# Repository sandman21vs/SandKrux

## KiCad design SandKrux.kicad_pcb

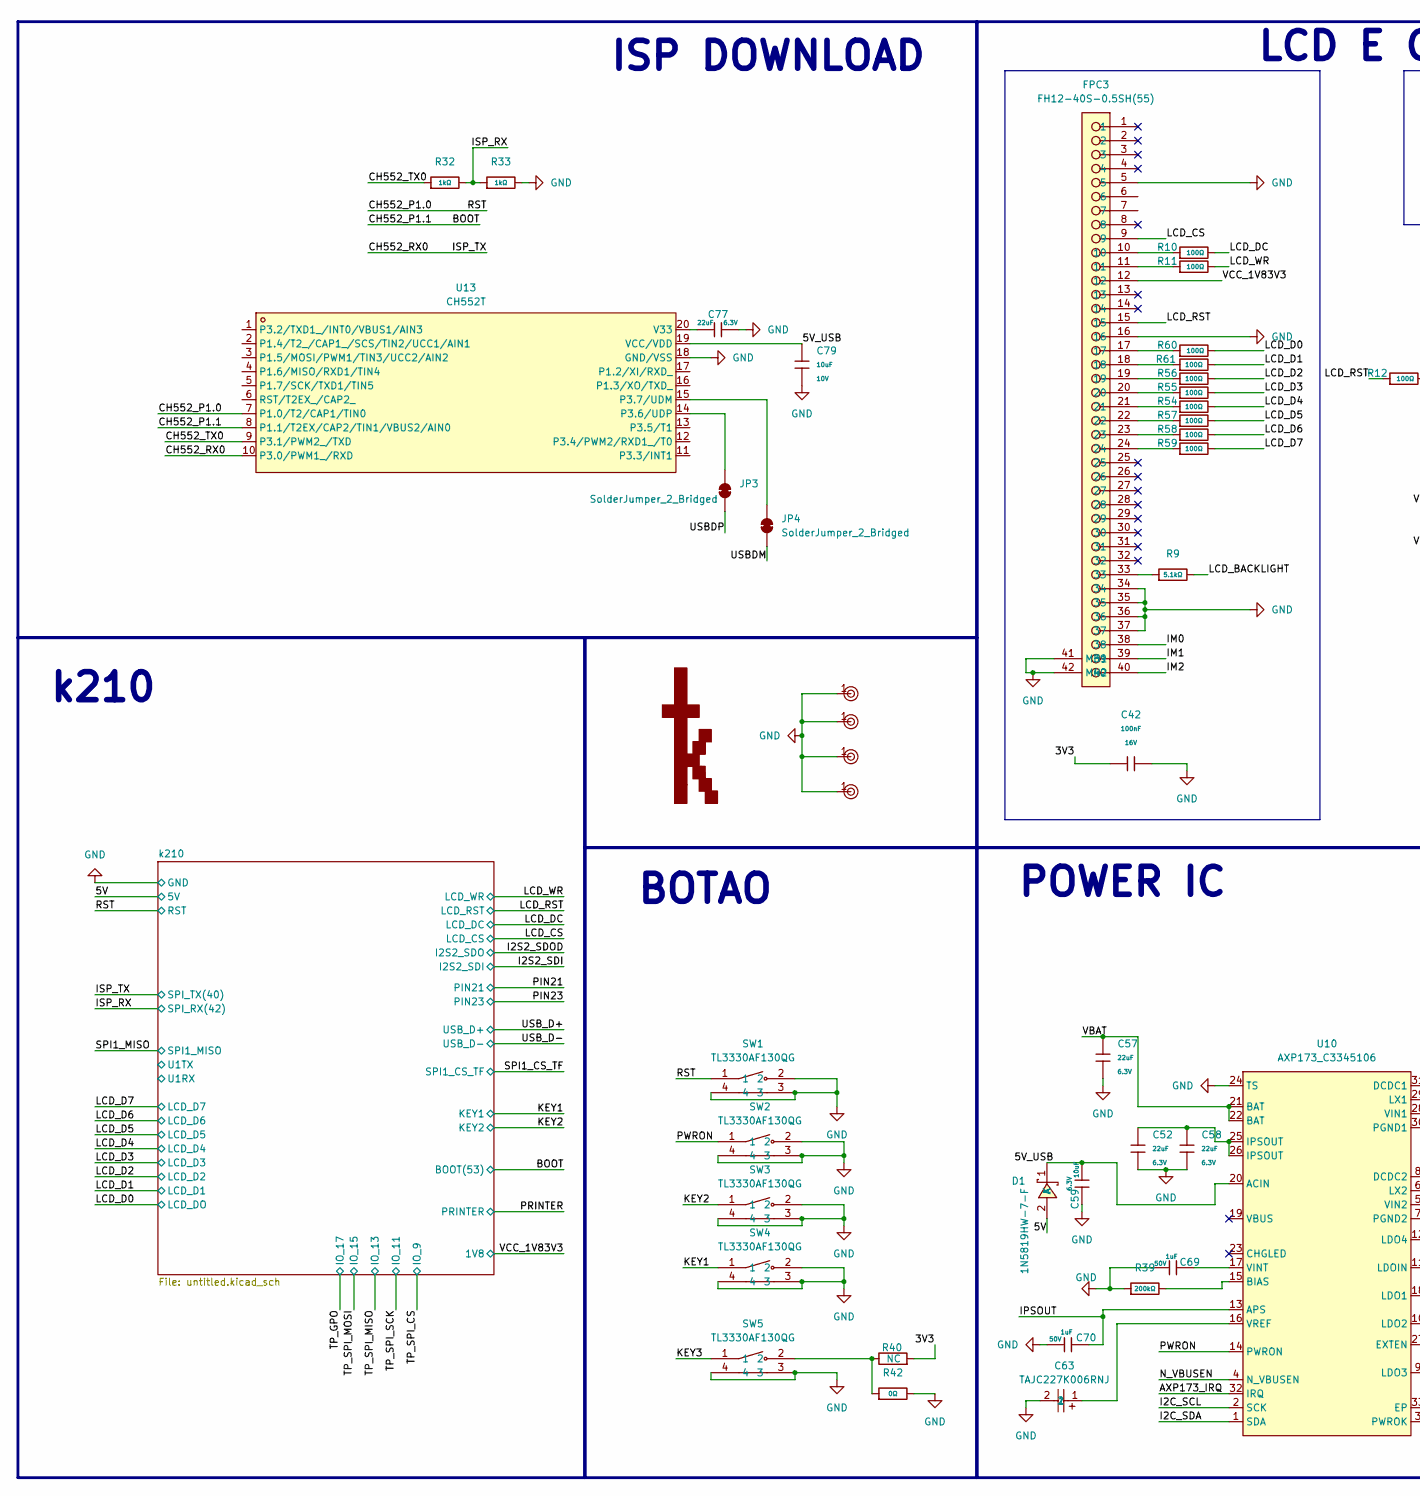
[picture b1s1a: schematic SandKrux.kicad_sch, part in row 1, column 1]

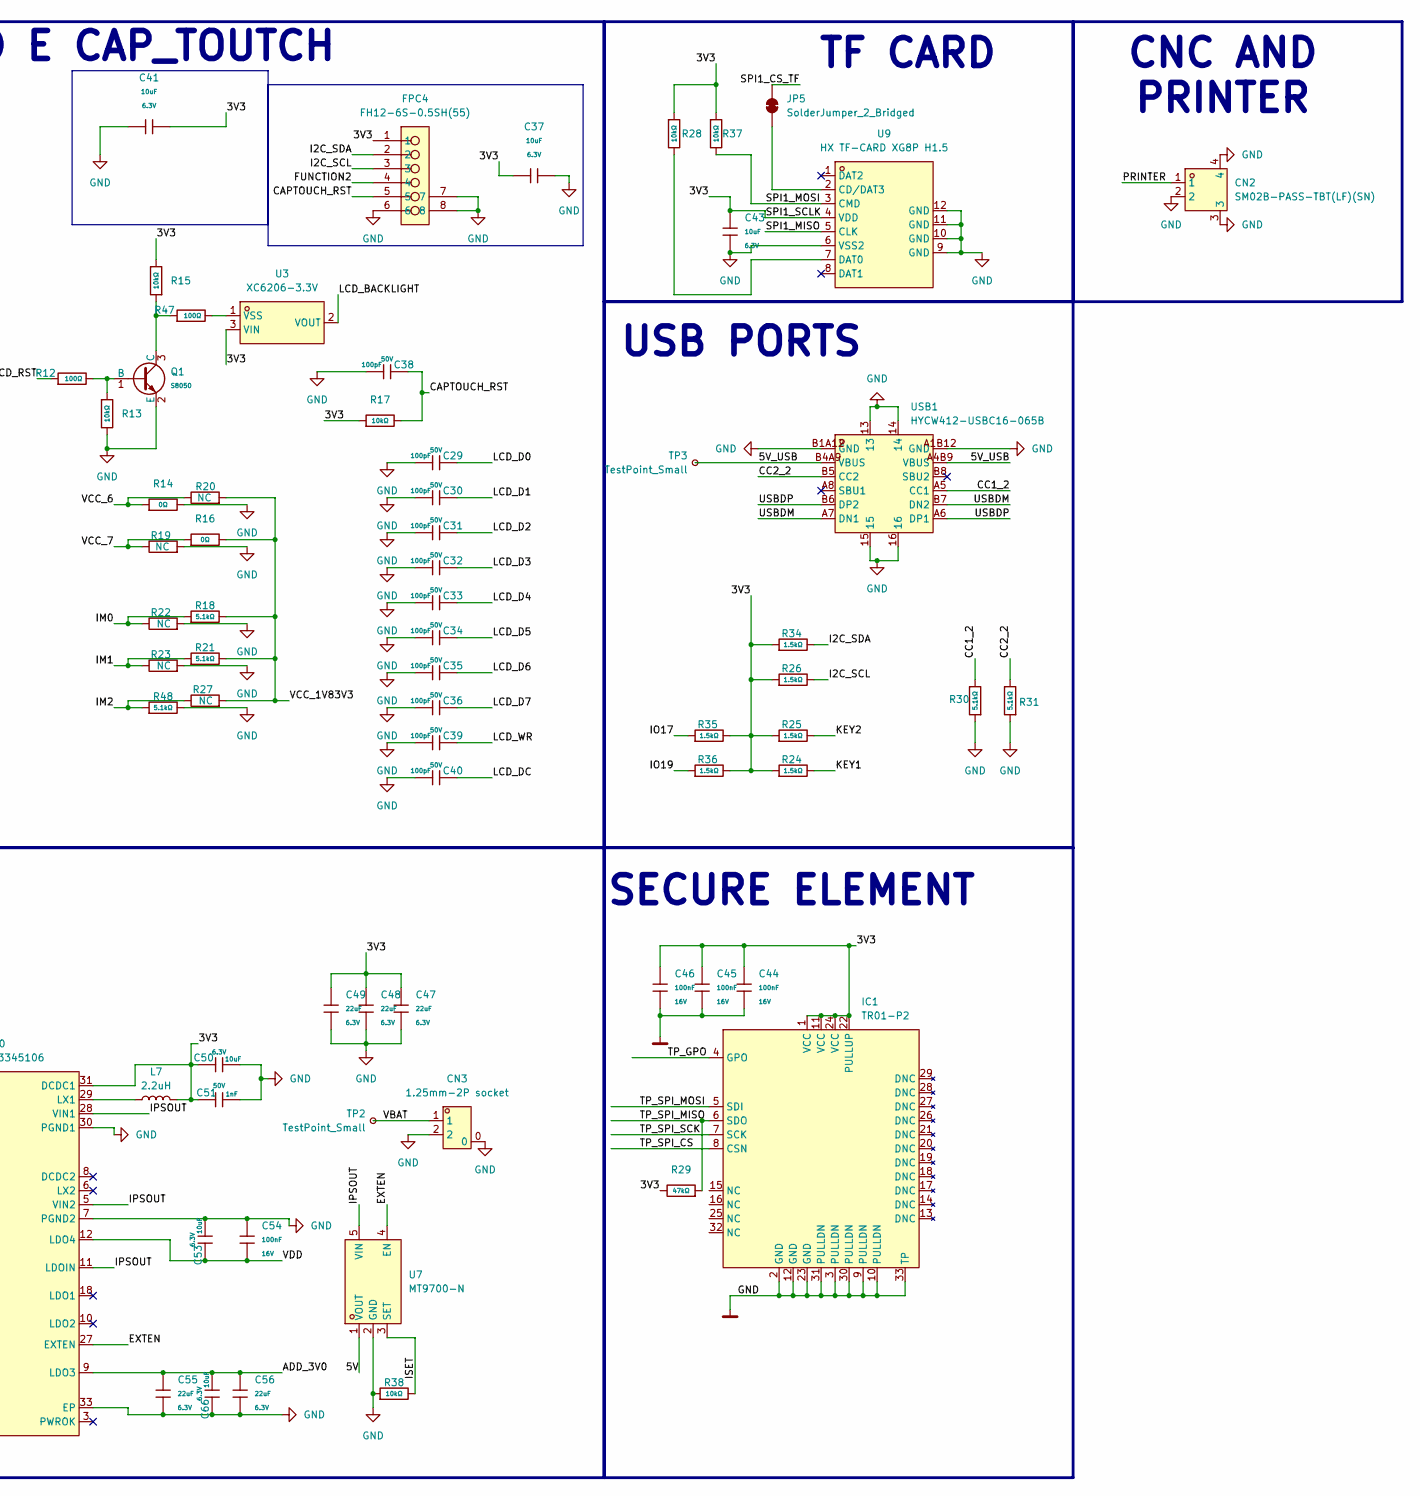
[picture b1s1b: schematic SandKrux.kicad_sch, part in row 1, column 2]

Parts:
C29, C30, C31, C32, C33, C34, C35, C36, C38, C39, C40: 100pF; C_0402; Voltage Rated 50V; Tolerance ±5%; Part 0402CG101J500NT; LCSC C1546
C37, C41, C43, C50, C53, C59, C66: 10uF; C_0402; Voltage Rated 6.3V; Tolerance ±20%; Part CL05A106MQ5NUNC; LCSC C15525
C42, C44, C45, C46, C54: 100nF; C_0402; Voltage Rated 16V; Tolerance ±10%; Part CL05B104KO5NNNC; LCSC C1525
C47, C48, C49, C52, C55, C56, C57, C58, C77: 22uF; C_0603; Voltage Rated 6.3V; Tolerance ±20%; Part CL10A226MQ8NRNC; LCSC C59461
C51: 1nF; C_0402; Voltage Rated 50V; Tolerance ±10%; Part 0402B102K500NT; LCSC C1523
C63: TAJC227K006RNJ; CAP-SMD_L6.0-W3.2-R-RD; LCSC Part C7216
C69, C70: 1uF; C_0603; Voltage Rated 50V; Tolerance ±10%; Part CL10A105KB8NNNC; LCSC C15849
C79: 10uF; C_0603; Voltage Rated 10V; Tolerance ±10%; Part CL10A106KP8NNNC; LCSC C19702
CN2: SM02B-PASS-TBT(LF)(SN); CONN-SMD_SM02B-PASS-TBT; LCSC Part C265417
CN3: 1.25mm-2P socket; CONN-SMD_1.25T-2P; LCSC Part C43462
D1: 1N5819HW-7-F; SOD-123_L2.7-W1.6-LS3.7-RD; LCSC Part C82544
FPC3: FH12-40S-0.5SH(55); FPC-SMD_FH12-40S-0.5SH-55; LCSC Part C202114
FPC4: FH12-6S-0.5SH(55); FPC-SMD_FH12-6S-0.5SH-55; LCSC Part C202118
H1, H2, H3, H4: Hole, 3mm
IC1: TR01-P2; QFN-32-1EP_4x4mm_P0.4mm_EP2.65x2.65mm
JP3, JP4, JP5: SolderJumper_2_Bridged; SolderJumper-2_P1.3mm_Bridged_RoundedPad1.0x1.5mm
L7: 2.2uH
Q1: S8050; Q_SOT-23; Part S8050; LCSC C364312
R9, R18, R21, R30, R31, R48: 5.1kΩ; R_0402; Overload Voltage (Max) 50V; Tolerance ±1%; Part 0402WGF5101TCE; LCSC C25905
R10, R11, R12, R47, R54, R55, R56, R57, R58, R59, R60, R61: 100Ω; R_0402; Overload Voltage (Max) 50V; Tolerance ±1%; Part 0402WGF1000TCE; LCSC C25076
R13, R15, R17, R28, R37, R38: 10kΩ; R_0402; Overload Voltage (Max) 50V; Tolerance ±1%; Part 0402WGF1002TCE; LCSC C25744
R14, R16, R42: 0Ω; R_0402; Overload Voltage (Max) 50V; Tolerance ±1%; Part 0402WGF0000TCE; LCSC C17168
R19, R20, R22, R23, R27, R40: NC; R_0201_0603Metric
R24, R25, R26, R34, R35, R36: 1.5kΩ; R_0402; Overload Voltage (Max) 50V; Tolerance ±1%; Part 0402WGF1501TCE; LCSC C25867
R29: 47kΩ; R_0402; Overload Voltage (Max) 50V; Tolerance ±1%; Part 0402WGF4702TCE; LCSC C25792
R32, R33: 1kΩ; R_0603; Overload Voltage (Max) 75V; Tolerance ±1%; Part 0603WAF1001T5E; LCSC C21190
R39: 200kΩ; R_0402; Overload Voltage (Max) 50V; Tolerance ±1%; Part 0402WGF2003TCE; LCSC C25764
SW1, SW2, SW3, SW4, SW5: TL3330AF130QG; SW-SMD_E-SWITCH_TL3330; LCSC Part C2886886
TP2, TP3: TestPoint_Small; TestPoint_Pad_D1.0mm
U3: XC6206-3.3V; SSOT-3_L2.9-W1.6-P0.95-LS2.8-BR; LCSC Part C2891841
U7: MT9700-N; SOT-23-5_L2.9-W1.6-P0.95-LS2.9-BL; LCSC Part C42441843
U9: HX TF-CARD XG8P H1.5; TF-SMD_HX-TF-CARD-XG8P-H1.5; LCSC Part C19189039
U10: AXP173_C3345106; QFN-32_L5.0-W5.0-P0.50-TL-EP3.5-1; LCSC Part C3345106
U13: CH552T; TSSOP-20_L6.5-W4.4-P0.65-LS6.4-BL; LCSC Part C111367
USB1: HYCW412-USBC16-065B; USB-C-SMD_HYCW412-USBC16-065B; LCSC Part C5342196

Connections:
/3V3: C37.1, C41.2, C42.1, C43.1, C44.1, C45.1, C46.1, C47.1, C48.1, C49.1, C50.1, C51.1, FPC4.1, IC1.1 (VCC), IC1.11 (VCC), IC1.22 (PULLUP), IC1.24 (VCC), L7.2, R15.2, R17.1, R24.1, R25.1, R26.1, R28.1, R29.2, R34.1, R35.2, R36.2, R37.1, R40.2, U3.3 (VIN), U9.4 (VDD), U10.31 (DCDC1)
/5V: D1.2 (A), U7.1 (VOUT); also elsewhere on the board
/5V_USB: C59.2, C79.1, D1.1 (K), TP3.1, U10.20 (ACIN), U13.19 (VCC/VDD), USB1.A4B9 (VBUS), USB1.B4A9 (VBUS)
/ADD_3V0: C55.1, C56.1, C66.2, U10.9 (LDO3)
/AXP173_IRQ: U10.32 (IRQ)
/BOOT: U13.8 (P1.1/T2EX/CAP2/TIN1/VBUS2/AIN0); also elsewhere on the board
/CAPTOUCH_RST: C38.2, FPC4.5, R17.2
/CC1_2: R30.2, USB1.A5 (CC1)
/CC2_2: R31.2, USB1.B5 (CC2)
/CH552_P1.0: SW1.1, U13.7 (P1.0/T2/CAP1/TIN0); also elsewhere on the board
/CH552_RX0: U13.10 (P3.0/PWM1_/RXD); also elsewhere on the board
/CH552_TX0: R32.1, U13.9 (P3.1/PWM2_/TXD)
/EXTEN: U7.4 (EN), U10.27 (EXTEN)
/FUNCTION2: FPC4.4
/I2C_SCL: FPC4.3, R26.2, U10.2 (SCK)
/I2C_SDA: FPC4.2, R34.2, U10.1 (SDA)
/IM0: FPC3.38, R18.1, R22.1
/IM1: FPC3.39, R21.1, R23.1
/IM2: FPC3.40, R27.1, R48.1
/IO17: R35.1
/IO19: R36.1
/IPSOUT: C70.2, U7.5 (VIN), U10.5 (VIN2), U10.11 (LDOIN), U10.13 (APS), U10.28 (VIN1)
/ISET: R38.2, U7.3 (SET)
/ISP_RX: R32.2, R33.1; also elsewhere on the board
/KEY1: R24.2, SW4.1; also elsewhere on the board
/KEY2: R25.2, SW3.1; also elsewhere on the board
/KEY3: SW5.1
/LCD_BACKLIGHT: R9.2, U3.2 (VOUT)
/LCD_CS: FPC3.9; also elsewhere on the board
/LCD_D0: C29.2, R60.2; also elsewhere on the board
/LCD_D1: C30.2, R61.2; also elsewhere on the board
/LCD_D2: C31.2, R56.2; also elsewhere on the board
/LCD_D3: C32.2, R55.2; also elsewhere on the board
/LCD_D4: C33.2, R54.2; also elsewhere on the board
/LCD_D5: C34.2, R57.2; also elsewhere on the board
/LCD_D6: C35.2, R58.2; also elsewhere on the board
/LCD_D7: C36.2, R59.2; also elsewhere on the board
/LCD_DC: C40.2, R10.2; also elsewhere on the board
/LCD_RST: FPC3.15, R12.1; also elsewhere on the board
/LCD_WR: C39.2, R11.2; also elsewhere on the board
/N_VBUSEN: U10.4 (N_VBUSEN)
/PRINTER: CN2.1; also elsewhere on the board
/PWRON: SW2.1, U10.14 (PWRON)
/SPI1_CS_TF: JP5.2 (B); also elsewhere on the board
/SPI1_MISO: U9.5 (CLK); also elsewhere on the board
/SPI1_MOSI: R37.2, U9.3 (CMD)
/TP_GPO: IC1.4 (GPO); also elsewhere on the board
/TP_SPI_CS: IC1.8 (CSN); also elsewhere on the board
/TP_SPI_MISO: IC1.6 (SDO), R29.1; also elsewhere on the board
/TP_SPI_MOSI: IC1.5 (SDI); also elsewhere on the board
/TP_SPI_SCK: IC1.7 (SCK); also elsewhere on the board
/USBDM: JP4.1 (A), USB1.A7 (DN1), USB1.B7 (DN2)
/USBDP: JP3.1 (A), USB1.A6 (DP1), USB1.B6 (DP2)
/VBAT: C57.1, CN3.1, TP2.1, U10.21 (BAT), U10.22 (BAT)
/VCC_1V83V3: FPC3.12, R16.2, R18.2, R20.2, R21.2, R27.2; also elsewhere on the board
/VCC_6: R14.1, R20.1
/VCC_7: R16.1, R19.1
/VDD: C53.1, C54.2, U10.12 (LDO4)
GND: C29.1, C30.1, C31.1, C32.1, C33.1, C34.1, C35.1, C36.1, C37.2, C38.1, C39.1, C40.1, C41.1, C42.2, C43.2, C44.2, C45.2, C46.2, C47.2, C48.2, C49.2, C50.2, C51.2, C52.2, C53.2, C54.1, C55.2, C56.2, C57.2, C58.2, C59.1, C63.2, C66.1, C69.1, C70.1, C77.2, C79.2, CN2.2, CN2.3, CN2.4, CN3.0, CN3.2, FPC3.5, FPC3.16, FPC3.34, FPC3.35, FPC3.36, FPC3.37, FPC3.41 (MH1), FPC3.42 (MH2), FPC4.6, FPC4.7, FPC4.8, H1.1, H2.1, H3.1, H4.1, IC1.2 (GND), IC1.3 (PULLDN), IC1.9 (PULLDN), IC1.10 (PULLDN), IC1.12 (GND), IC1.23 (GND), IC1.30 (PULLDN), IC1.31 (PULLDN), IC1.33 (TP), Q1.2 (E), R13.2, R14.2, R19.2, R22.2, R23.2, R30.1, R31.1, R33.2, R38.1, R39.1, R42.2, R48.2, SW1.2, SW1.3, SW1.4, SW2.2, SW2.3, SW2.4, SW3.2, SW3.3, SW3.4, SW4.2, SW4.3, SW4.4, SW5.3, SW5.4, U7.2 (GND), U9.6 (VSS2), U9.9 (GND), U9.10 (GND), U9.11 (GND), U9.12 (GND), U10.7 (PGND2), U10.24 (TS), U10.30 (PGND1), U10.33 (EP), U13.18 (GND/VSS), USB1.13, USB1.14, USB1.15, USB1.16, USB1.A1B12 (GND), USB1.B1A12 (GND); also elsewhere on the board
unnamed: C52.1, C58.1, U10.25 (IPSOUT), U10.26 (IPSOUT)
unnamed: FPC3.10, R10.1
unnamed: FPC3.11, R11.1
unnamed: FPC3.17, R60.1
unnamed: FPC3.18, R61.1
unnamed: FPC3.19, R56.1
unnamed: FPC3.20, R55.1
unnamed: FPC3.21, R54.1
unnamed: FPC3.22, R57.1
unnamed: FPC3.23, R58.1
unnamed: FPC3.24, R59.1
unnamed: FPC3.33, R9.1
unnamed: JP3.2 (B), U13.14 (P3.6/UDP)
unnamed: JP4.2 (B), U13.15 (P3.7/UDM)
unnamed: JP5.1 (A), U9.2 (CD/DAT3)
unnamed: Q1.1 (B), R12.2, R13.1
unnamed: Q1.3 (C), R15.1, R47.1
unnamed: R40.1, R42.1, SW5.2
unnamed: R47.2, U3.1 (VSS)
unnamed: R28.2, U9.7 (DAT0)
unnamed: R39.2, U10.15 (BIAS)
unnamed: L7.1, U10.29 (LX1)
unnamed: C69.2, U10.17 (VINT)
unnamed: C63.1, U10.16 (VREF)
unnamed: C77.1, U13.20 (V33)

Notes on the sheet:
TF CARD
LCD E CAP_TOUTCH
POWER IC
BOTAO
k210
ISP DOWNLOAD
USB PORTS
SECURE ELEMENT
CNC AND PRINTER

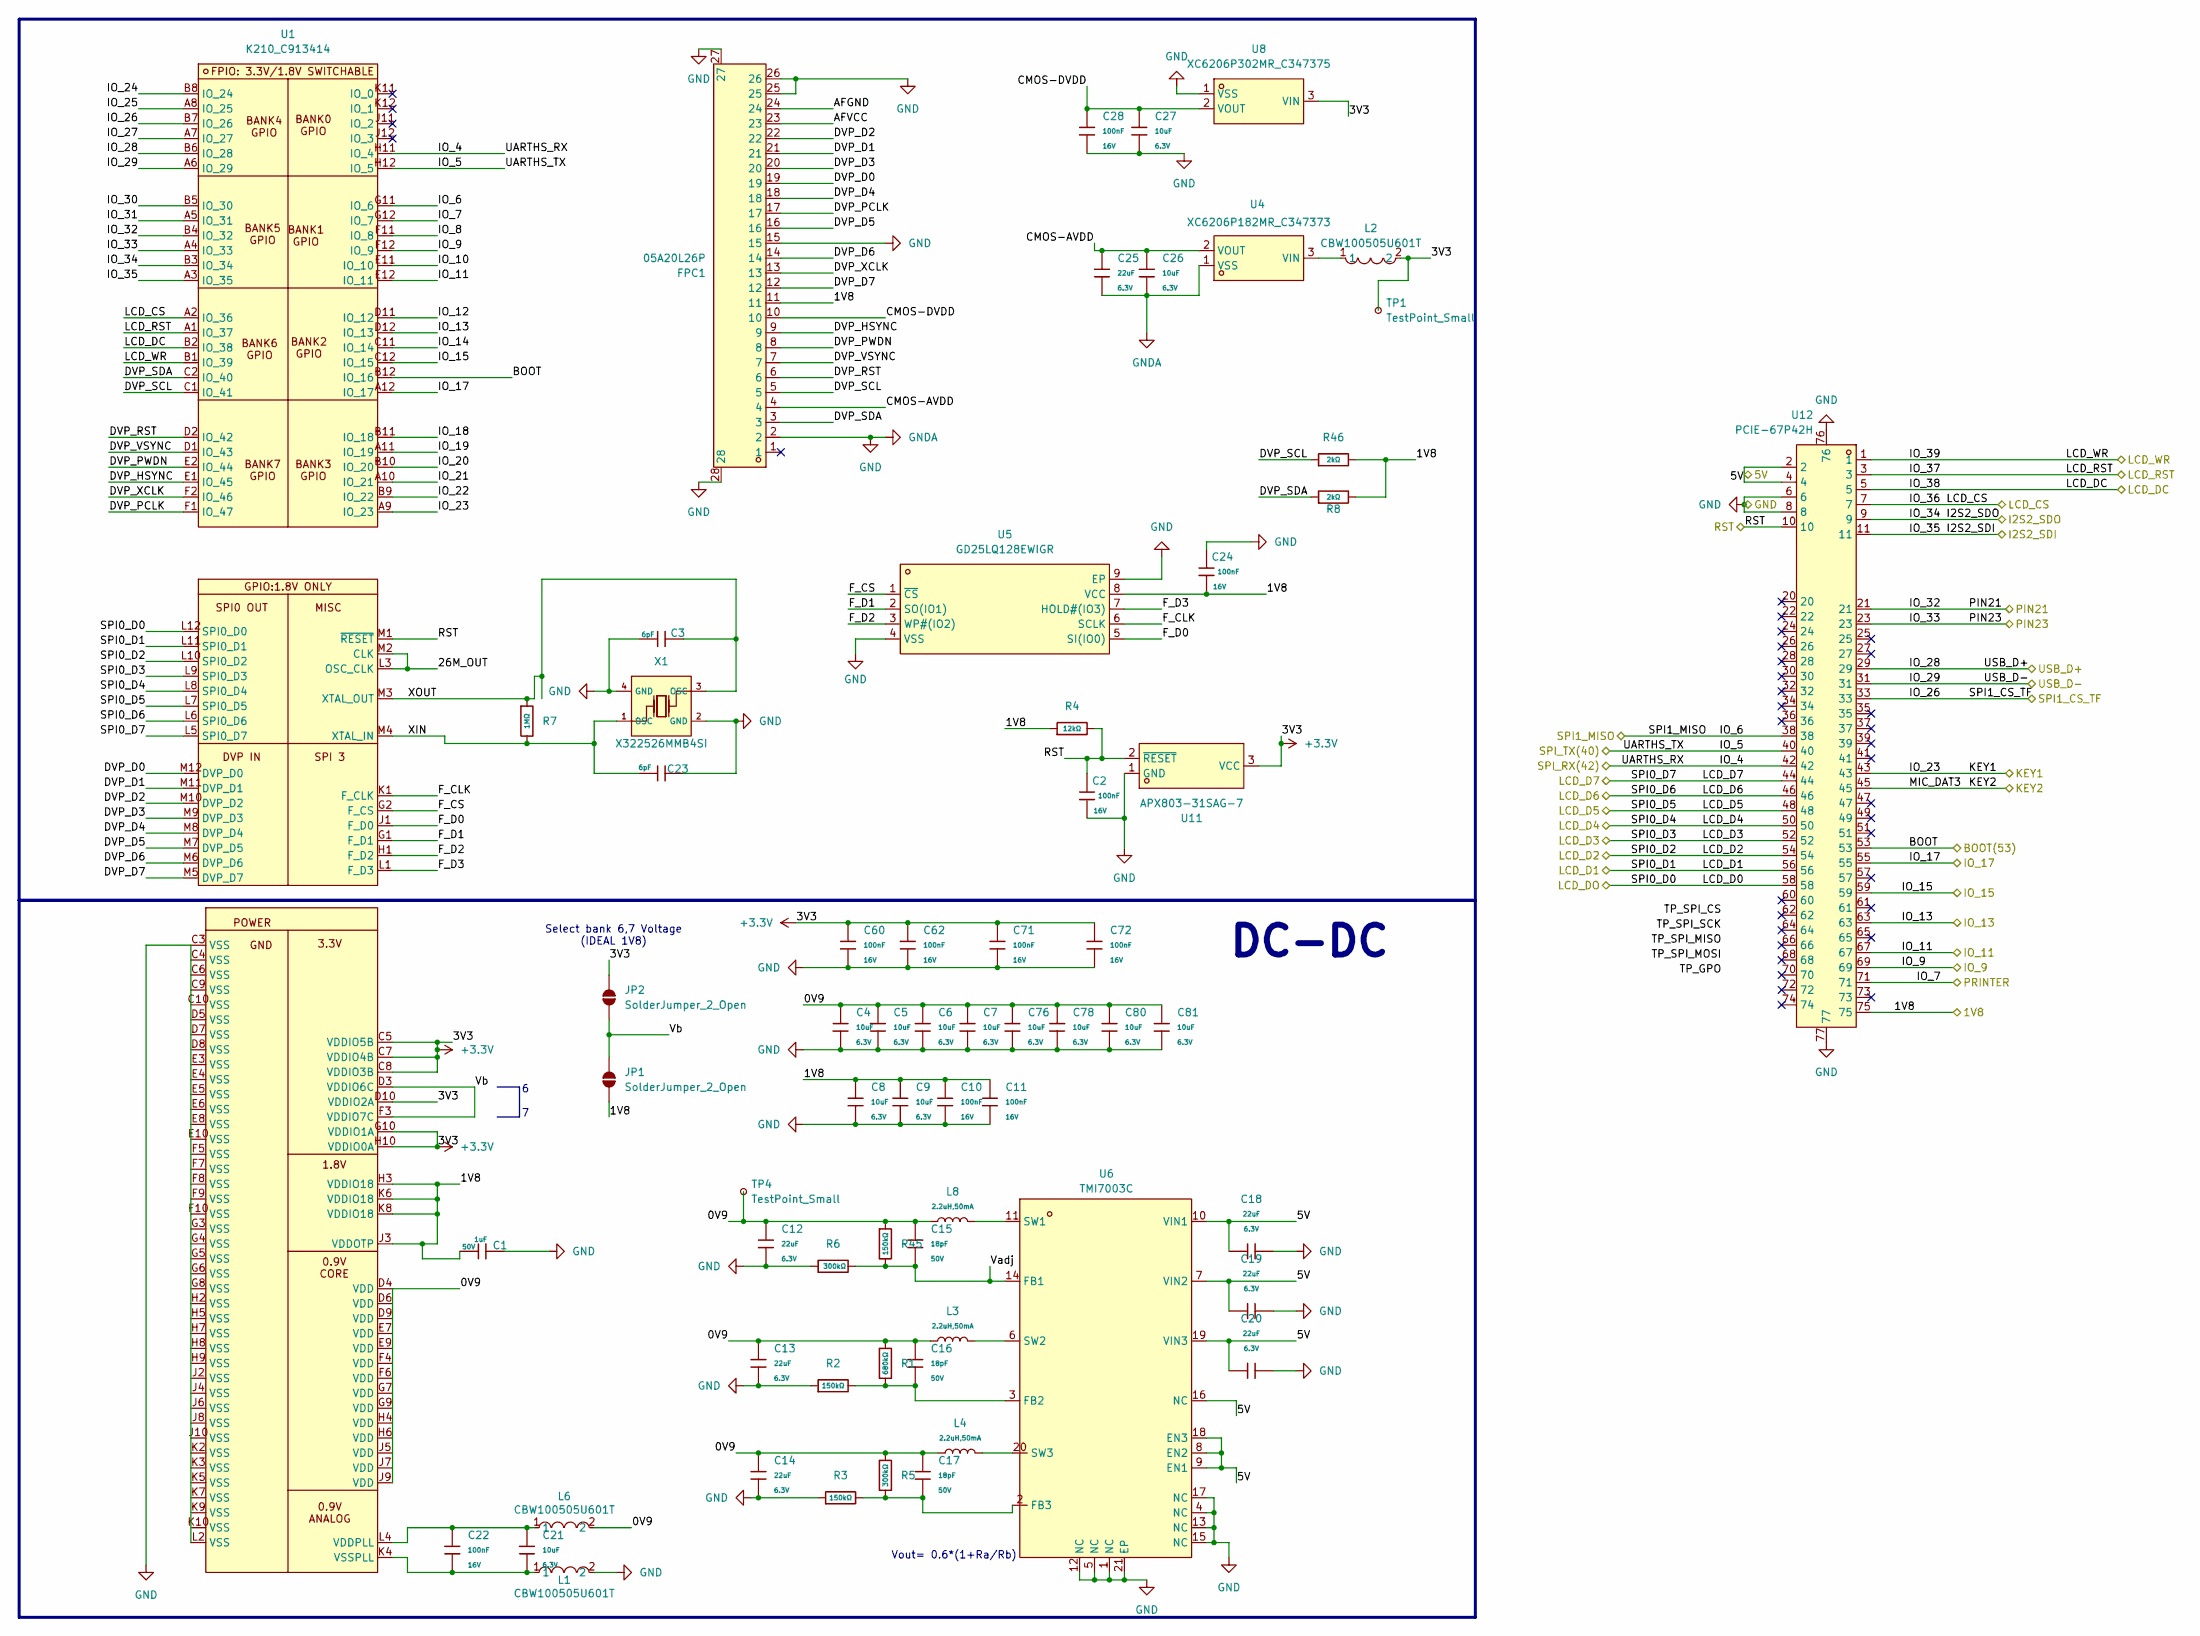
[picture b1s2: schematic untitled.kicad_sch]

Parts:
C1: 1uF; C_0603; Voltage Rated 50V; Tolerance ±10%; Part CL10A105KB8NNNC; LCSC C15849
C2, C10, C11, C22, C24, C28, C60, C62, C71, C72: 100nF; C_0402; Voltage Rated 16V; Tolerance ±10%; Part CL05B104KO5NNNC; LCSC C1525
C3, C23: 6pF; C_0402; Part 0402CG6R0C500NT (SMT业务专用); LCSC C30274
C4, C5, C6, C7, C8, C9, C21, C26, C27, C76, C78, C80, C81: 10uF; C_0402; Voltage Rated 6.3V; Tolerance ±20%; Part CL05A106MQ5NUNC; LCSC C15525
C12, C13, C14, C18, C19, C20, C25: 22uF; C_0603; Voltage Rated 6.3V; Tolerance ±20%; Part CL10A226MQ8NRNC; LCSC C59461
C15, C16, C17: 18pF; C_0402; Voltage Rated 50V; Tolerance ±5%; Part 0402CG180J500NT; LCSC C1549
FPC1: 05A20L26P; FPC-SMD_05A20L26P; LCSC Part C25503114
JP1, JP2: SolderJumper_2_Open; SolderJumper-2_P1.3mm_Open_RoundedPad1.0x1.5mm
L1, L2, L6: CBW100505U601T; L0402; LCSC Part C124083
L3, L4, L8: 2.2uH,50mA; L_0805; Tolerance ±10%; Part CMI201209U2R2KT; LCSC C1043
R1: 680kΩ; R_0603; Overload Voltage (Max) 75V; Tolerance ±1%; Part 0603WAF6803T5E; LCSC C25822
R2, R3, R45: 150kΩ; R_0402; Overload Voltage (Max) 50V; Tolerance ±1%; Part 0402WGF1503TCE; LCSC C25755
R4: 12kΩ; R_0402; Overload Voltage (Max) 50V; Tolerance ±1%; Part 0402WGF1202TCE; LCSC C25752
R5, R6: 300kΩ; R_0402; Overload Voltage (Max) 50V; Tolerance ±1%; Part 0402WGF3003TCE; LCSC C25774
R7: 1MΩ; R_0402; Overload Voltage (Max) 50V; Tolerance ±1%; Part 0402WGF1004TCE; LCSC C26083
R8, R46: 2kΩ; R_0402; Overload Voltage (Max) 50V; Tolerance ±1%; Part 0402WGF2001TCE; LCSC C4109
TP1, TP4: TestPoint_Small; TestPoint_Pad_D1.0mm
U1: K210_C913414; BGA-144_L8.0-W8.0-R12-C12-P0.65-BL; LCSC Part C913414
U4: XC6206P182MR_C347373; SOT-23-3_L3.0-W1.7-P0.95-LS2.9-BR; LCSC Part C347373
U5: GD25LQ128EWIGR; WSON-8_L6.0-W5.0-P1.27-BL-EP; LCSC Part C2928889
U6: TMI7003C; QFN-20_L3.0-W3.0-P0.40-BL-EP1.7; LCSC Part C840566
U8: XC6206P302MR_C347375; SOT-23-3_L3.0-W1.7-P0.95-LS2.9-BR; LCSC Part C347375
U11: APX803-31SAG-7; SOT-23-3_L2.9-W1.3-P1.90-LS2.4-BR; LCSC Part C460552
U12: PCIE-67P42H; PCIE-SMD_75P-P0.50_HYC01B-05NGFF-420; LCSC Part C19188865
X1: X322526MMB4SI; CRYSTAL-SMD_4P-L3.2-W2.5-BL; Frequency Tolerance ±10ppm; Part X322512MSB4SI; LCSC C15192

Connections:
+3.3V: C60.1, C62.1, C71.1, C72.1, JP2.1 (A), L2.2, TP1.1, U1.C5 (VDDIO5B), U1.C7 (VDDIO4B), U1.C8 (VDDIO3B), U1.D10 (VDDIO2A), U1.G10 (VDDIO1A), U1.H10 (VDDIO0A), U8.3 (VIN), U11.3 (VCC)
/5V: C18.1, C19.1, C20.1, U6.7 (VIN2), U6.8 (EN2), U6.9 (EN1), U6.10 (VIN1), U6.16 (NC), U6.18 (EN3), U6.19 (VIN3), U12.2, U12.4; also elsewhere on the board
/BOOT: U1.B12 (IO_16), U12.53; also elsewhere on the board
/CH552_P1.0: C2.2, R4.2, U1.M1 (~RESET), U11.2 (~RESET), U12.10; also elsewhere on the board
/CH552_RX0: U1.H12 (IO_5), U12.40; also elsewhere on the board
/I2S2_SDI: U1.A3 (IO_35), U12.11
/I2S2_SDOD: U1.B3 (IO_34), U12.9
/ISP_RX: U1.H11 (IO_4), U12.42; also elsewhere on the board
/KEY1: U1.A9 (IO_23), U12.43; also elsewhere on the board
/KEY2: U12.45; also elsewhere on the board
/LCD_CS: U1.A2 (IO_36), U12.7; also elsewhere on the board
/LCD_D0: U1.L12 (SPI0_D0), U12.58; also elsewhere on the board
/LCD_D1: U1.L11 (SPI0_D1), U12.56; also elsewhere on the board
/LCD_D2: U1.L10 (SPI0_D2), U12.54; also elsewhere on the board
/LCD_D3: U1.L9 (SPI0_D3), U12.52; also elsewhere on the board
/LCD_D4: U1.L8 (SPI0_D4), U12.50; also elsewhere on the board
/LCD_D5: U1.L7 (SPI0_D5), U12.48; also elsewhere on the board
/LCD_D6: U1.L6 (SPI0_D6), U12.46; also elsewhere on the board
/LCD_D7: U1.L5 (SPI0_D7), U12.44; also elsewhere on the board
/LCD_DC: U1.B2 (IO_38), U12.5; also elsewhere on the board
/LCD_RST: U1.A1 (IO_37), U12.3; also elsewhere on the board
/LCD_WR: U1.B1 (IO_39), U12.1; also elsewhere on the board
/PIN21: U1.B4 (IO_32), U12.21
/PIN23: U1.A4 (IO_33), U12.23
/PRINTER: U1.G12 (IO_7), U12.71; also elsewhere on the board
/SPI1_CS_TF: U1.B7 (IO_26), U12.33; also elsewhere on the board
/SPI1_MISO: U1.G11 (IO_6), U12.38; also elsewhere on the board
/TP_GPO: U1.A12 (IO_17), U12.55; also elsewhere on the board
/TP_SPI_CS: U1.F12 (IO_9), U12.69; also elsewhere on the board
/TP_SPI_MISO: U1.D12 (IO_13), U12.63; also elsewhere on the board
/TP_SPI_MOSI: U1.C12 (IO_15), U12.59; also elsewhere on the board
/TP_SPI_SCK: U1.E12 (IO_11), U12.67; also elsewhere on the board
/USB_D+: U1.B6 (IO_28), U12.29
/USB_D-: U1.A6 (IO_29), U12.31
/VCC_1V83V3: C1.1, C8.1, C9.1, C10.1, C11.1, C24.1, FPC1.11, JP1.2 (B), R4.1, R8.2, R46.2, U1.H3 (VDDIO18), U1.J3 (VDDOTP), U1.K6 (VDDIO18), U1.K8 (VDDIO18), U5.8 (VCC), U12.75; also elsewhere on the board
/k210/0V9: C4.1, C5.1, C6.1, C7.1, C12.1, C13.1, C14.1, C15.1, C16.1, C17.1, C76.1, C78.1, C80.1, C81.1, L3.1, L4.1, L6.2, L8.1, R1.1, R5.1, R45.1, TP4.1, U1.D4 (VDD), U1.J9 (VDD)
/k210/26M_OUT: U1.L3 (OSC_CLK), U1.M2 (CLK)
/k210/AFGND: FPC1.24
/k210/AFVCC: FPC1.23
/k210/CMOS-AVDD: C25.1, C26.1, FPC1.4, U4.2 (VOUT)
/k210/CMOS-DVDD: C27.1, C28.1, FPC1.10, U8.2 (VOUT)
/k210/DVP_D0: FPC1.19, U1.M12 (DVP_D0)
/k210/DVP_D1: FPC1.21, U1.M11 (DVP_D1)
/k210/DVP_D2: FPC1.22, U1.M10 (DVP_D2)
/k210/DVP_D3: FPC1.20, U1.M9 (DVP_D3)
/k210/DVP_D4: FPC1.18, U1.M8 (DVP_D4)
/k210/DVP_D5: FPC1.16, U1.M7 (DVP_D5)
/k210/DVP_D6: FPC1.14, U1.M6 (DVP_D6)
/k210/DVP_D7: FPC1.12, U1.M5 (DVP_D7)
/k210/DVP_HSYNC: FPC1.9, U1.E1 (IO_45)
/k210/DVP_PCLK: FPC1.17, U1.F1 (IO_47)
/k210/DVP_PWDN: FPC1.8, U1.E2 (IO_44)
/k210/DVP_RST: FPC1.6, U1.D2 (IO_42)
/k210/DVP_SCL: FPC1.5, R46.1, U1.C1 (IO_41)
/k210/DVP_SDA: FPC1.3, R8.1, U1.C2 (IO_40)
/k210/DVP_VSYNC: FPC1.7, U1.D1 (IO_43)
/k210/DVP_XCLK: FPC1.13, U1.F2 (IO_46)
/k210/F_CLK: U1.K1 (F_CLK), U5.6 (SCLK)
/k210/F_CS: U1.G2 (F_CS), U5.1 (~CS)
/k210/F_D0: U1.J1 (F_D0), U5.5 (SI(IO0))
/k210/F_D1: U1.G1 (F_D1), U5.2 (SO(IO1))
/k210/F_D2: U1.H1 (F_D2), U5.3 (WP#(IO2))
/k210/F_D3: U1.L1 (F_D3), U5.7 (HOLD#(IO3))
/k210/IO_8: U1.F11 (IO_8)
/k210/IO_10: U1.E11 (IO_10)
/k210/IO_12: U1.D11 (IO_12)
/k210/IO_14: U1.C11 (IO_14)
/k210/IO_18: U1.B11 (IO_18)
/k210/IO_19: U1.A11 (IO_19)
/k210/IO_20: U1.B10 (IO_20)
/k210/IO_21: U1.A10 (IO_21)
/k210/IO_22: U1.B9 (IO_22)
/k210/IO_24: U1.B8 (IO_24)
/k210/IO_25: U1.A8 (IO_25)
/k210/IO_27: U1.A7 (IO_27)
/k210/IO_30: U1.B5 (IO_30)
/k210/IO_31: U1.A5 (IO_31)
/k210/Vadj: C15.2, R6.2, R45.2, U6.14 (FB1)
/k210/Vb: JP1.1 (A), JP2.2 (B), U1.D3 (VDDIO6C), U1.F3 (VDDIO7C)
/k210/XIN: C23.1, R7.2, U1.M4 (XTAL_IN), X1.1 (OSC)
/k210/XOUT: C3.2, R7.1, U1.M3 (XTAL_OUT), X1.3 (OSC)
GND: C1.2, C2.1, C3.1, C4.2, C5.2, C6.2, C7.2, C8.2, C9.2, C10.2, C11.2, C12.2, C13.2, C14.2, C18.2, C19.2, C20.2, C23.2, C24.2, C25.2, C26.2, C27.2, C28.2, C60.2, C62.2, C71.2, C72.2, C76.2, C78.2, C80.2, C81.2, FPC1.2, FPC1.15, FPC1.25, FPC1.26, FPC1.27, FPC1.28, L1.2, R2.1, R3.1, R6.1, U1.C3 (VSS), U1.L2 (VSS), U4.1 (VSS), U5.4 (VSS), U5.9 (EP), U6.1 (NC), U6.4 (NC), U6.5 (NC), U6.12 (NC), U6.13 (NC), U6.15 (NC), U6.17 (NC), U6.21 (EP), U8.1 (VSS), U11.1 (GND), U12.6, U12.8, U12.76, U12.77, X1.2 (GND), X1.4 (GND); also elsewhere on the board
unnamed: C21.1, C22.1, L6.1, U1.L4 (VDDPLL)
unnamed: C21.2, C22.2, L1.1, U1.K4 (VSSPLL)
unnamed: L2.1, U4.3 (VIN)
unnamed: C16.2, R1.2, R2.2, U6.3 (FB2)
unnamed: C17.2, R3.2, R5.2, U6.2 (FB3)
unnamed: L8.2, U6.11 (SW1)
unnamed: L3.2, U6.6 (SW2)
unnamed: L4.2, U6.20 (SW3)

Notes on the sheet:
6 7
Select bank 6,7 Voltage (IDEAL 1V8)
DC-DC
Vout= 0.6*(1+Ra/Rb)

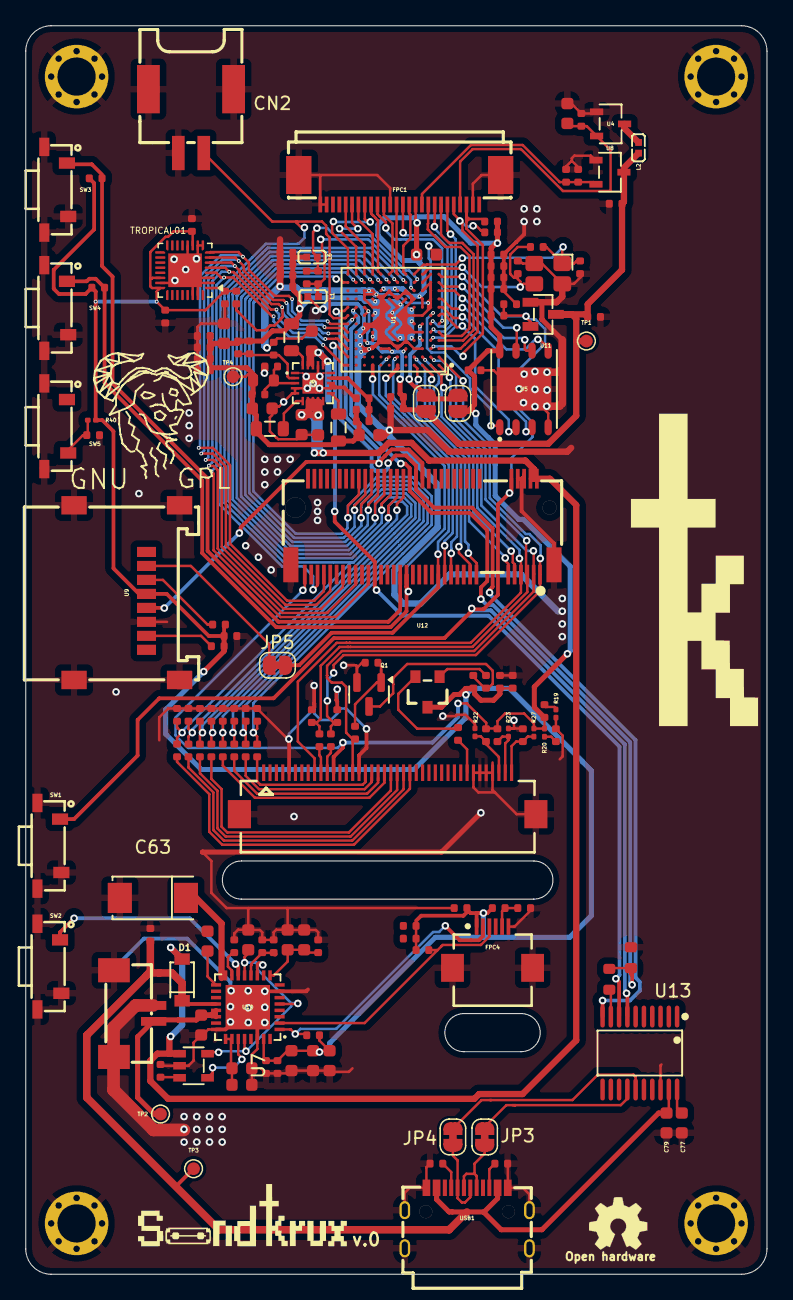
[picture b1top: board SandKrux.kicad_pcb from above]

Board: 2 copper layers, 58.3 x 98.2 mm, 173 parts (0 on the bottom side), 122 nets.

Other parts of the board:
Sign_OSHW_7.3x6.0mm: Sign_OSHW_7.3x6.0mm; Sign_OSHW_7.3x6.0mmn

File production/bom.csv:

Designator,Footprint,Quantity,Value,LCSC Part #
"C1, C69, C70",C_0603,3,1uF,C15849
"C10, C11, C2, C22, C24, C28, C42, C44, C45, C46, C54, C60, C62, C71, C72",C_0402,15,100nF,C1525
"C12, C13, C14, C18, C19, C20, C25, C47, C48, C49, C52, C55, C56, C57, C58, C77",C_0603,16,22uF,C59461
"C15, C16, C17",C_0402,3,18pF,C1549
"C21, C26, C27, C37, C4, C41, C43, C5, C50, C53, C59, C6, C66, C7, C76, C78, C8, C80, C81, C9",C_0402,20,10uF,C15525
"C23, C3",C_0402,2,6pF,C30274
"C29, C30, C31, C32, C33, C34, C35, C36, C38, C39, C40",C_0402,11,100pF,C1546
C51,C_0402,1,1nF,C1523
C63,CAP-SMD_L6.0-W3.2-R-RD,1,TAJC227K006RNJ,C7216
C79,C_0603,1,10uF,C19702
CN2,CONN-SMD_SM02B-PASS-TBT,1,SM02B-PASS-TBT(LF)(SN),C265417
CN3,CONN-SMD_1.25T-2P,1,1.25mm-2P socket,C43462
D1,SOD-123_L2.7-W1.6-LS3.7-RD,1,1N5819HW-7-F,C82544
FPC1,FPC-SMD_05A20L26P,1,05A20L26P,C25503114
FPC3,FPC-SMD_FH12-40S-0.5SH-55,1,FH12-40S-0.5SH(55),C202114
FPC4,FPC-SMD_FH12-6S-0.5SH-55,1,FH12-6S-0.5SH(55),C202118
"H1, H2, H3, H4","Hole, 3mm",4,~,
IC1,QFN-32-1EP_4x4mm_P0.4mm_EP2.65x2.65mm,1,TROPIC01_chip,
"L1, L2, L6",L0402,3,CBW100505U601T,C124083
"L3, L4, L8",L_0805,3,"2.2uH,50mA",C1043
Q1,Q_SOT-23,1,S8050,C364312
R1,R_0603,1,680kΩ,C25822
"R10, R11, R12, R47, R54, R55, R56, R57, R58, R59, R60, R61",R_0402,12,100Ω,C25076
"R13, R15, R17, R28, R37, R38",R_0402,6,10kΩ,C25744
"R14, R16, R42",R_0402,3,0Ω,C17168
"R18, R21, R30, R31, R48, R9",R_0402,6,5.1kΩ,C25905
"R19, R20, R22, R23, R27, R40",0201,6,NC,
"R2, R3, R45",R_0402,3,150kΩ,C25755
"R24, R25, R26, R34, R35, R36",R_0402,6,1.5kΩ,C25867
R29,R_0402,1,47kΩ,C25792
"R32, R33",R_0603,2,1kΩ,C21190
R39,R_0402,1,200kΩ,C25764
R4,R_0402,1,12kΩ,C25752
"R46, R8",R_0402,2,2kΩ,C4109
"R5, R6",R_0402,2,300kΩ,C25774
R7,R_0402,1,1MΩ,C26083
"SW1, SW2, SW3, SW4, SW5",SW-SMD_E-SWITCH_TL3330,5,TL3330AF130QG,C2886886
"TP1, TP2, TP3, TP4",TestPoint_Pad_D1.0mm,4,TestPoint_Small,
U1,BGA-144_L8.0-W8.0-R12-C12-P0.65-BL,1,K210_C913414,C913414
U10,QFN-32_L5.0-W5.0-P0.50-TL-EP3.5-1,1,AXP173_C3345106,C3345106
U11,SOT-23-3_L2.9-W1.3-P1.90-LS2.4-BR,1,APX803-31SAG-7,C460552
U12,PCIE-SMD_75P-P0.50_HYC01B-05NGFF-420,1,PCIE-67P42H,C19188865
U13,TSSOP-20_L6.5-W4.4-P0.65-LS6.4-BL,1,CH552T,C111367
U3,SSOT-3_L2.9-W1.6-P0.95-LS2.8-BR,1,XC6206-3.3V,C2891841
U4,SOT-23-3_L3.0-W1.7-P0.95-LS2.9-BR,1,XC6206P182MR_C347373,C347373
U5,WSON-8_L6.0-W5.0-P1.27-BL-EP,1,GD25LQ128EWIGR,C2928889
U6,QFN-20_L3.0-W3.0-P0.40-BL-EP1.7,1,TMI7003C,C840566
U7,SOT-23-5_L2.9-W1.6-P0.95-LS2.9-BL,1,MT9700-N,C42441843
U8,SOT-23-3_L3.0-W1.7-P0.95-LS2.9-BR,1,XC6206P302MR_C347375,C347375
U9,TF-SMD_HX-TF-CARD-XG8P-H1.5,1,HX TF-CARD XG8P H1.5,C19189039
USB1,USB-C-SMD_HYCW412-USBC16-065B,1,HYCW412-USBC16-065B,C5342196
X1,CRYSTAL-SMD_4P-L3.2-W2.5-BL,1,X322526MMB4SI,C15192

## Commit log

2026-02-08 camera suport
2026-02-08 organizacao basica dos componentes na pcb
2026-02-10 LCD E CAP_TOUTCH E JLC DOWNLOADER
2026-02-15 reposicionamento de componentes
2026-02-17 NGFF 67p conector no esquematico
2026-02-24 fios e vias lcd toutch botoes e o q mais estava conectado ao modulo m2 alem da coexao m2 com k210
2026-02-28 correcao de erros nas vias
2026-03-05 ch340
2026-03-07 `distribuicao de cabos e 3d arrumado
2026-03-09 troca de resistores por pecas jlcpcb
2026-03-10 TROPCAL 01 CONECTIO E ATUALIZACAO E SUBSTITUICAO DE COMPONENTES POR COMPONENTES JLC DISPONIVEIS
